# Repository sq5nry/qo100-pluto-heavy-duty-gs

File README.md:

### qo100-pluto-heavy-duty-gs

# Hello fellow QO-100 aficionados,
Here's another realization of a ground station based on <a href="https://wiki.analog.com/university/tools/pluto/hacking/hardware#revision_b" target="_blank">Pluto</a>. Designed as a sturdy box to be thrown on your roof requires just a single Ethernet cable to talk to. It hosts the great <a href="https://github.com/F1ATB/Remote-SDR" target="_blank">F1ATB Remote-SDR</a> web-based transceiver but when roaming in your LAN you can also enjoy the <a href="https://www.sdr-radio.com/console" target="_blank">G4ELI SDR Console</a> desktop application. Pluto is running on a customized firmware from <a href="https://www.f5uii.net/wp-content/uploads/2021/03/pluto.zip" target="_blank">F5UII</a>. Assemblage of assorted open-source candies makes for a comfortable phone operation.

The device has four panel sockets:
- **RJ-45**: Ethernet+PoE
- **N**: 2.4GHz transmitter output
- **F**: input from LNB
- **SMA**: GPS active antenna

Features:
- operation via a web browser incl. full duplex and live waterfall display
- direct network access to Pluto for 3rd party applications
- push-to-talk automation
- frequency stability from GPS Disciplined Oscillator
- power from PoE only

:warning:Remote operation possible after meeting <a href="https://forum.amsat-dl.org/index.php?thread/3234-remote-operation-via-qo-100/" target="_blank">AMSAT requirements</a>. For the on-demand immediate shutdown capability I'm using a Wi-Fi plug to cut off AC from the PoE injector.

| deployment example               | inside the box |
|----------------------------------|----------|
|  |  |

# Operation
1. Connect to a router with DHCP server via 802.3bt PoE injector offering 90W. 15 meters of SSTP CAT6 works fine. The Raspberry host will be reachable under hostname `remsdr-rpi4`. Configure remote access (eg port forwarding or <a href="https://www.zerotier.com" target="_blank">ZeroTier VPN</a> - installed)
2. Configure the web access <a href="https://remsdr-rpi4/settings.html"  target="_blank">https://remsdr-rpi4/settings.html</a> as described in <a href="https://f1atb.fr/remote-sdr-v5-raspberry-4b-or-orange-pi-image-installation/" target="_blank">https://f1atb.fr/remote-sdr-v5-raspberry-4b-or-orange-pi-image-installation</a>. Finally, navigate to the start page <a href="https://remsdr-rpi4" target="_blank">https://remsdr-rpi4</a>.
3. Alternatively, connect to Pluto locally by specifying `ip:remsdr-rpi4` as the address. Parallel use with the web interface mostly won't work.\
 For SDR Console follow the <a href="https://www.sdr-radio.com/EsHail-2" target="_blank">configuration manual</a>. Connect the USB push-to-talk button and volume knob for best experience.
 
| Arduino Due MIDI controller      |
|----------------------------------|
|  |

:warning: Smooth remote work when talking directly to Pluto (eg. SDR Console) requires a low-jitter 20Mbps connection to stream the whole 500kHz NB transponder. Web interface will settle for an ordinary 512kbps link.

# Troubleshooting
1. Restart Pluto via web interface
2. Try turning it off and on again using your remote AC switch. Pluto and software on RPi becomes operational within a minute.
3. Check GPS status on the dashboard panel inside the box
4. Log in via SSH to conduct further diagnosis

# Service manual
General block diagram: [main.pdf](hw-block-diagrams/main.pdf)

## Pluto SDR
Built on top of rev. 'B' with two modules added inside the Pluto enclosure: external clock input and PTT output. Flashed with a firmware from F5UII https://www.f5uii.net/wp-content/uploads/2021/03/pluto.zip, here used only for the PTT when working with SDR Console. PTT is active when GPO0 is high and GPO1 is low to counteract transients on Pluto boot (read more here https://hf5l.pl/adalm-pluto-do-qo100-i-nie-tylko/). Here's ready module employing an 817 optocoupler:  \
Schematics diagram: [pluto_ptt.pdf](hw-pluto-ptt/pluto_ptt.pdf)

To install this extension, drill a hole in Pluto's plastic wall and mount a Cinch connector. Fix the PCB by tightening it via existing hole with a longer screw to the mainboard with a 5mm plastic spacer.

External clock feed for Pluto is designed by DM5RM https://forum.amsat-dl.org/index.php?thread/3199-external-clock-for-adalm-pluto/. Operation hinges on a clever idea of creating a small DC component from the clock signal for switching inputs between internal oscillator (not very stable for transmitting) and external one. I've added a blue LED informing that the external clock is active. External clock is generated by GPSDO. There's a blocking capacitor before the isolating transformer as the GPSDO Si5351 output stage doesn't like DC shorts.

Schematics diagram: [pluto_clock_buffer-sch.pdf](hw-pluto-ext-clock/pluto_clock_buffer-sch.pdf) \
To install this extension, drill a hole in Pluto's plastic wall and tight fit an SMA edge connector between RX and TX ports. Place additional insulation tape to avoid bridging grounds of the SMA and that of Pluto. Use a short IPEX pigtail between the SMA connector and the board. Wire four terminal posts parallel to the onboard oscillator (1.8V, OUT, E/D, GND). Fix the PCB by tightening it via existing hole in a similar manner as the PTT extension. Place another wire from USB for 5V supply (attach to the filtering cap as shown in the picture); this line also routes to the PTT board.

A no-name 2.4GHz power amplifier delivers abt. 10W at 24V & 2A. It is mounted on a heatsink, further pressed against the enclosure wall. Internally it comprises three stages: SAW filter, MMIC pre-amplifier, and final stage with a directional coupler for forward power measurement. PTT powers the MMIC and biases the final stage hence the ~90mA current consumption.

Receive path consists of an LNB and the bias-tee. I have added an option of switching LNA voltage for H/V polarisation control, for future wideband use.
 \
Schematics diagram: [pluto_biastee.pdf](hw-biastee-lna/pluto_biastee.pdf)

Finally, Pluto is powered from two USB plugs as advised by ADI.

## Raspberry Pi 4B
The platform is running the image from F1ATB https://f1atb.fr/remote-sdr-v5-raspberry-4b-or-orange-pi-image-installation/ and is serving a web-based Remote SDR application for receiving and transmitting via Pluto. In addition, Pluto's libiio endpoint is exposed externally so that you can connect to it via SDR Console or another client. In this mode, RPi is acting as a router between Pluto's network and RPi host. One GPIO pin is the PTT output and connects to the control board. \
Network script for exposing Pluto over RPi's ethernet interface: [ext-pluto](scripts/ext-pluto). Copy it under _/etc/network/interfaces_.

## Power and PTT control
Power supply is provided from a power regulator of the PoE splitter, preset to 24V and rated at 90W max. It goes directly to:
- the 2.4GHz power amplifier
- bias-tee and LNA power regulator
- 5V 8A regulator for all other modules

Each downstream line is protected by a resettable polymer fuse. \
Schematics diagram: [pluto_pwr_ctrl.pdf](hw-psu-ctrl/pluto_pwr_ctrl.pdf) 

| 5V regulator close-up                           |
|-------------------------------------------------|
|  |

On the same board is mounted PTT circuitry that sums both PTT inputs (from RPi GPIO and Pluto PTT) and switches on PTT voltage for PA (abt. 90mA of current consumption). Q1 and Q2 form a high-side switch where the first stage is actually a two-transistor wired-OR gate with the second transistor being the optocoupler inside Pluto. You'll have noticed that the PTT coming from RPi's GPIO is unnecessary since Pluto tells you when it's transmitting by activating the optocoupler. Yet you might not want to upgrade the firmware which adds this and stay with the web-application only. Another reason is PTT via GPIO is asserted as soon as you click PTT on the web page and it may take tenths of milliseconds if by Pluto. This delay is virtually unnoticeable when working in SDR Console.

## GPSDO
Based on projects of W3PM (https://github.com/W3PM/GPS-Si5351-VFO-QEX-JUL-AUG-2015), SQ1GU (http://sq1gu.tobis.com.pl/pl/syntezery-dds/44-generator-si5351a) and SP3VSS (https://sp3vss.eu/moje-konstrukcje/gpsdo-generator-synchronizowany-gps/).
It generates fixed 40MHz frequency _disciplined_ by the GPS PPS signal and consists of three common-off-the-shelf modules: Arduino Nano (a clone), Si5351 synthesizer and a GPS receiver.
This is a minimal implementation of the oscillator, without display and buttons. I have introduced the following changes to the source code:
- removed handling of display and buttons
- added initial frequency correction (about 4kHz) so that at least one synchronization round can be saved. Value is hardcoded and based on a coarse one-time measurement.
- added a duplicated PPS output via GPIO for diagnostics which drives a LED at 0,5Hz and 50% duty.
- code refactoring and clean-up

Sketch: [gpsdo_minimal.ino](hw-gpsdo/gpsdo_minimal.ino) \
Block diagram: [gpsdo.pdf](hw-gpsdo/gpsdo.pdf) \
 \
Output spectrum: 
The spectrum shows a decent pattern for square wave harmonics, however 2nd order components are relatively high and decay only up to -50dBc at 1GHz. Notable are numerous spikes spaced at 200kHz, most probably being a residue from the internal Si5351 PLL stage. I haven't noticed any audible difference between this GPSDO and internal Pluto clock when working on the narrowband transponder. Wideband use might require a cleaner signal with respect to the jitter but I haven't checked that.

The diagnostics board houses two LEDs showing status of the GPSDO:
- pulse-per-second indicator showing the GPS receiver has signal
- high-accuracy (<1Hz) lock achieved

In addition:
- red LED when TX is engaged
- bargraph for TX output level

## Transmit button and volume knob
SDR Console application accepts MIDI-based devices to control transceiver functions. A simple implementation for PTT and volume knob can be realized using an Arduino module supporting a USB device natively. I've used a clone: _Due R3 SAM3X8E CORTEX-M3_. 
I based on the project presented here: https://go.musiconerd.com/code-gen-basic \
Sketch: [midi_controller_Duo_v2.ino](sw-midi-ctrl%2Fmidi_controller_Duo_v2/midi_controller_Duo_v2.ino)

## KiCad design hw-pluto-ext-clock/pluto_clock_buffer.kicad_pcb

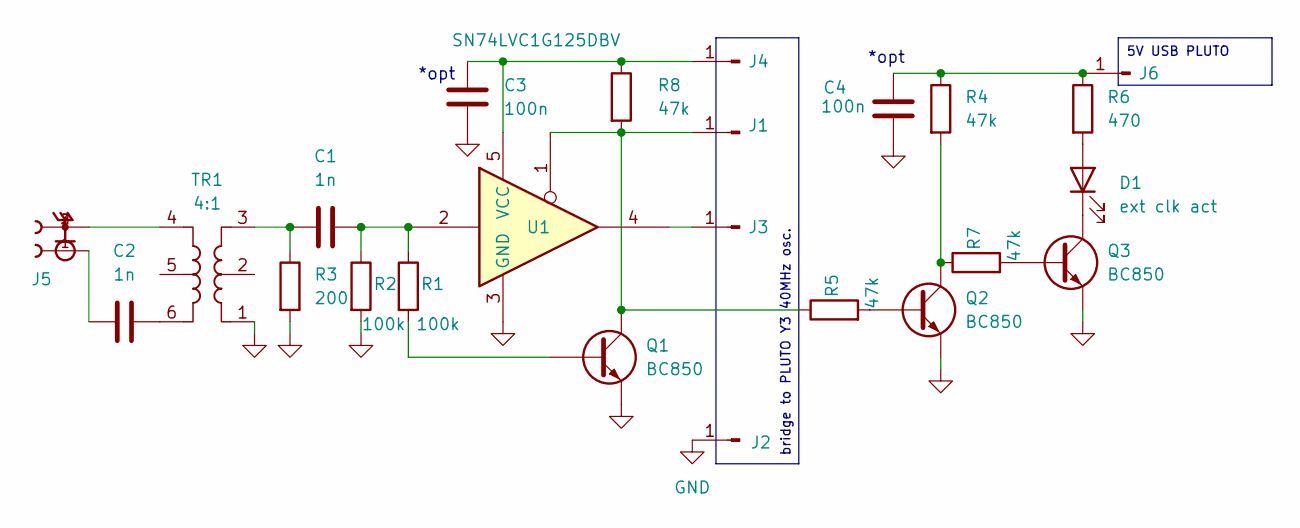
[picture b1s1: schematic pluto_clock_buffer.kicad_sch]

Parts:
C1, C2: 1n; C_0805_2012Metric
C3, C4: 100n; C_0805_2012Metric
D1: ext clk act; LED_0603_1608Metric
J1, J2, J3, J4, J6: Conn_01x01_Pin; Pin_D1.0mm_L10.0mm
J5: 20279-001E-03; IPEX_20279-001E-03; PARTREV 32
Q1, Q2, Q3: BC850; SOT-323_SC-70_Handsoldering
R1, R2: 100k; R_0603_1608Metric
R3: 200; R_0603_1608Metric
R4, R5, R7, R8: 47k; R_0603_1608Metric
R6: 470; R_0603_1608Metric
TR1: 4:1; Mini-Circuits_CD637_H5.23mm
U1: SN74LVC1G125DBV; SOT-23-5

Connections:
GND: C3.2, C4.2, J2.1, Q1.2 (E), Q2.2 (E), Q3.2 (E), R2.2, R3.2, TR1.1, U1.3 (GND)
unnamed: C1.1, R1.1, R2.1, U1.2
unnamed: C1.2, R3.1, TR1.3
unnamed: C2.1, TR1.6
unnamed: C2.2, J5.1
unnamed: D1.2 (A), R6.2
unnamed: D1.1 (K), Q3.3 (C)
unnamed: J1.1, Q1.3 (C), R5.1, R8.2, U1.1
unnamed: J3.1, U1.4
unnamed: C3.1, J4.1, R8.1, U1.5 (VCC)
unnamed: J5.2, J5.3, TR1.4
unnamed: C4.1, J6.1, R4.1, R6.1
unnamed: Q1.1 (B), R1.2
unnamed: Q2.1 (B), R5.2
unnamed: Q2.3 (C), R4.2, R7.1
unnamed: Q3.1 (B), R7.2

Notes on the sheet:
5V USB PLUTO
bridge to PLUTO Y3 40MHz osc.
*opt

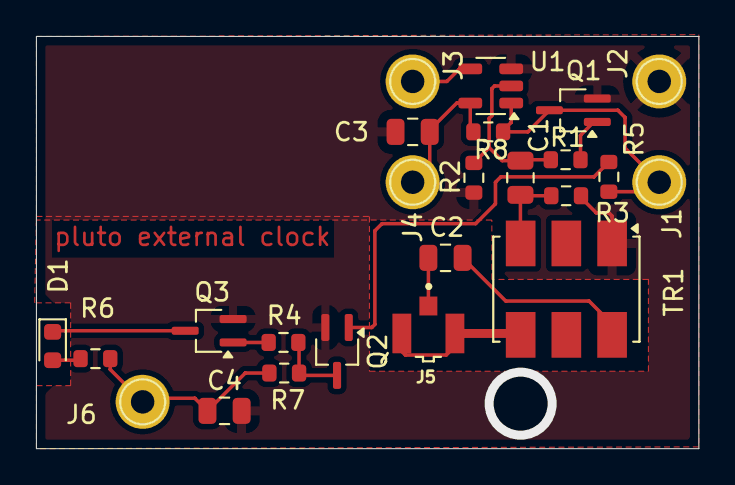
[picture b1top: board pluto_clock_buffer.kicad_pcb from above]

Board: 2 copper layers, 36.8 x 22.9 mm, 24 parts (0 on the bottom side), 16 nets.

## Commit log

2024-08-24 feat: initial commit
2024-08-24 feat: pictures and gpsdo sketch
2024-08-25 feat: midi control for sdr console
2024-08-25 gitignore
2024-08-25 pics
2024-08-26 readme
    pics
2024-08-26 renames
2024-08-28 network script for externalizing pluto
2024-08-31 readme: updates
    bash script sonar fixes
2024-08-31 readme: updates
2024-08-31 readme: pl
    WIP
2024-09-01 readme: pl and updates
2024-09-01 readme: link updates
2024-09-11 fix: fw rules for local link also
2024-09-11 readme: bom-pl
2024-10-02 bom humidity script
2024-10-28 readme: humidity sensor
